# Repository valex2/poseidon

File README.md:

# poseidon
Stanford Robosub 🏄‍♂️🐳🌊 Electrical Subsystem Repository

[Website](https://www.stanfordrobosub.org/)

[Block Diagram](https://drive.google.com/file/d/1UzBXgo1StivMrRFJ6YxzVo7dkJmS1rf_/view?usp=sharing)

# Important notes
## Thrusters
DO NOT RUN THRUSTERS AT FULL POWER FOR THE TIME BEING - 20 to 30% max

DO NOT RUN FOR MORE THAN 10 SECONDS WHILE OUTSIDE OF WATER

## Comms
We are using a Teensy 4.1 that communicates with the Orin over a serial port.

Use serial library in Python, and write as follows:
> portName.write(b"thruster_number delay_value")

### Thruster PWM Assignment
- 1100 us is full reverse thrust
- 1500 us is off
- 1900 us is full forward thrust

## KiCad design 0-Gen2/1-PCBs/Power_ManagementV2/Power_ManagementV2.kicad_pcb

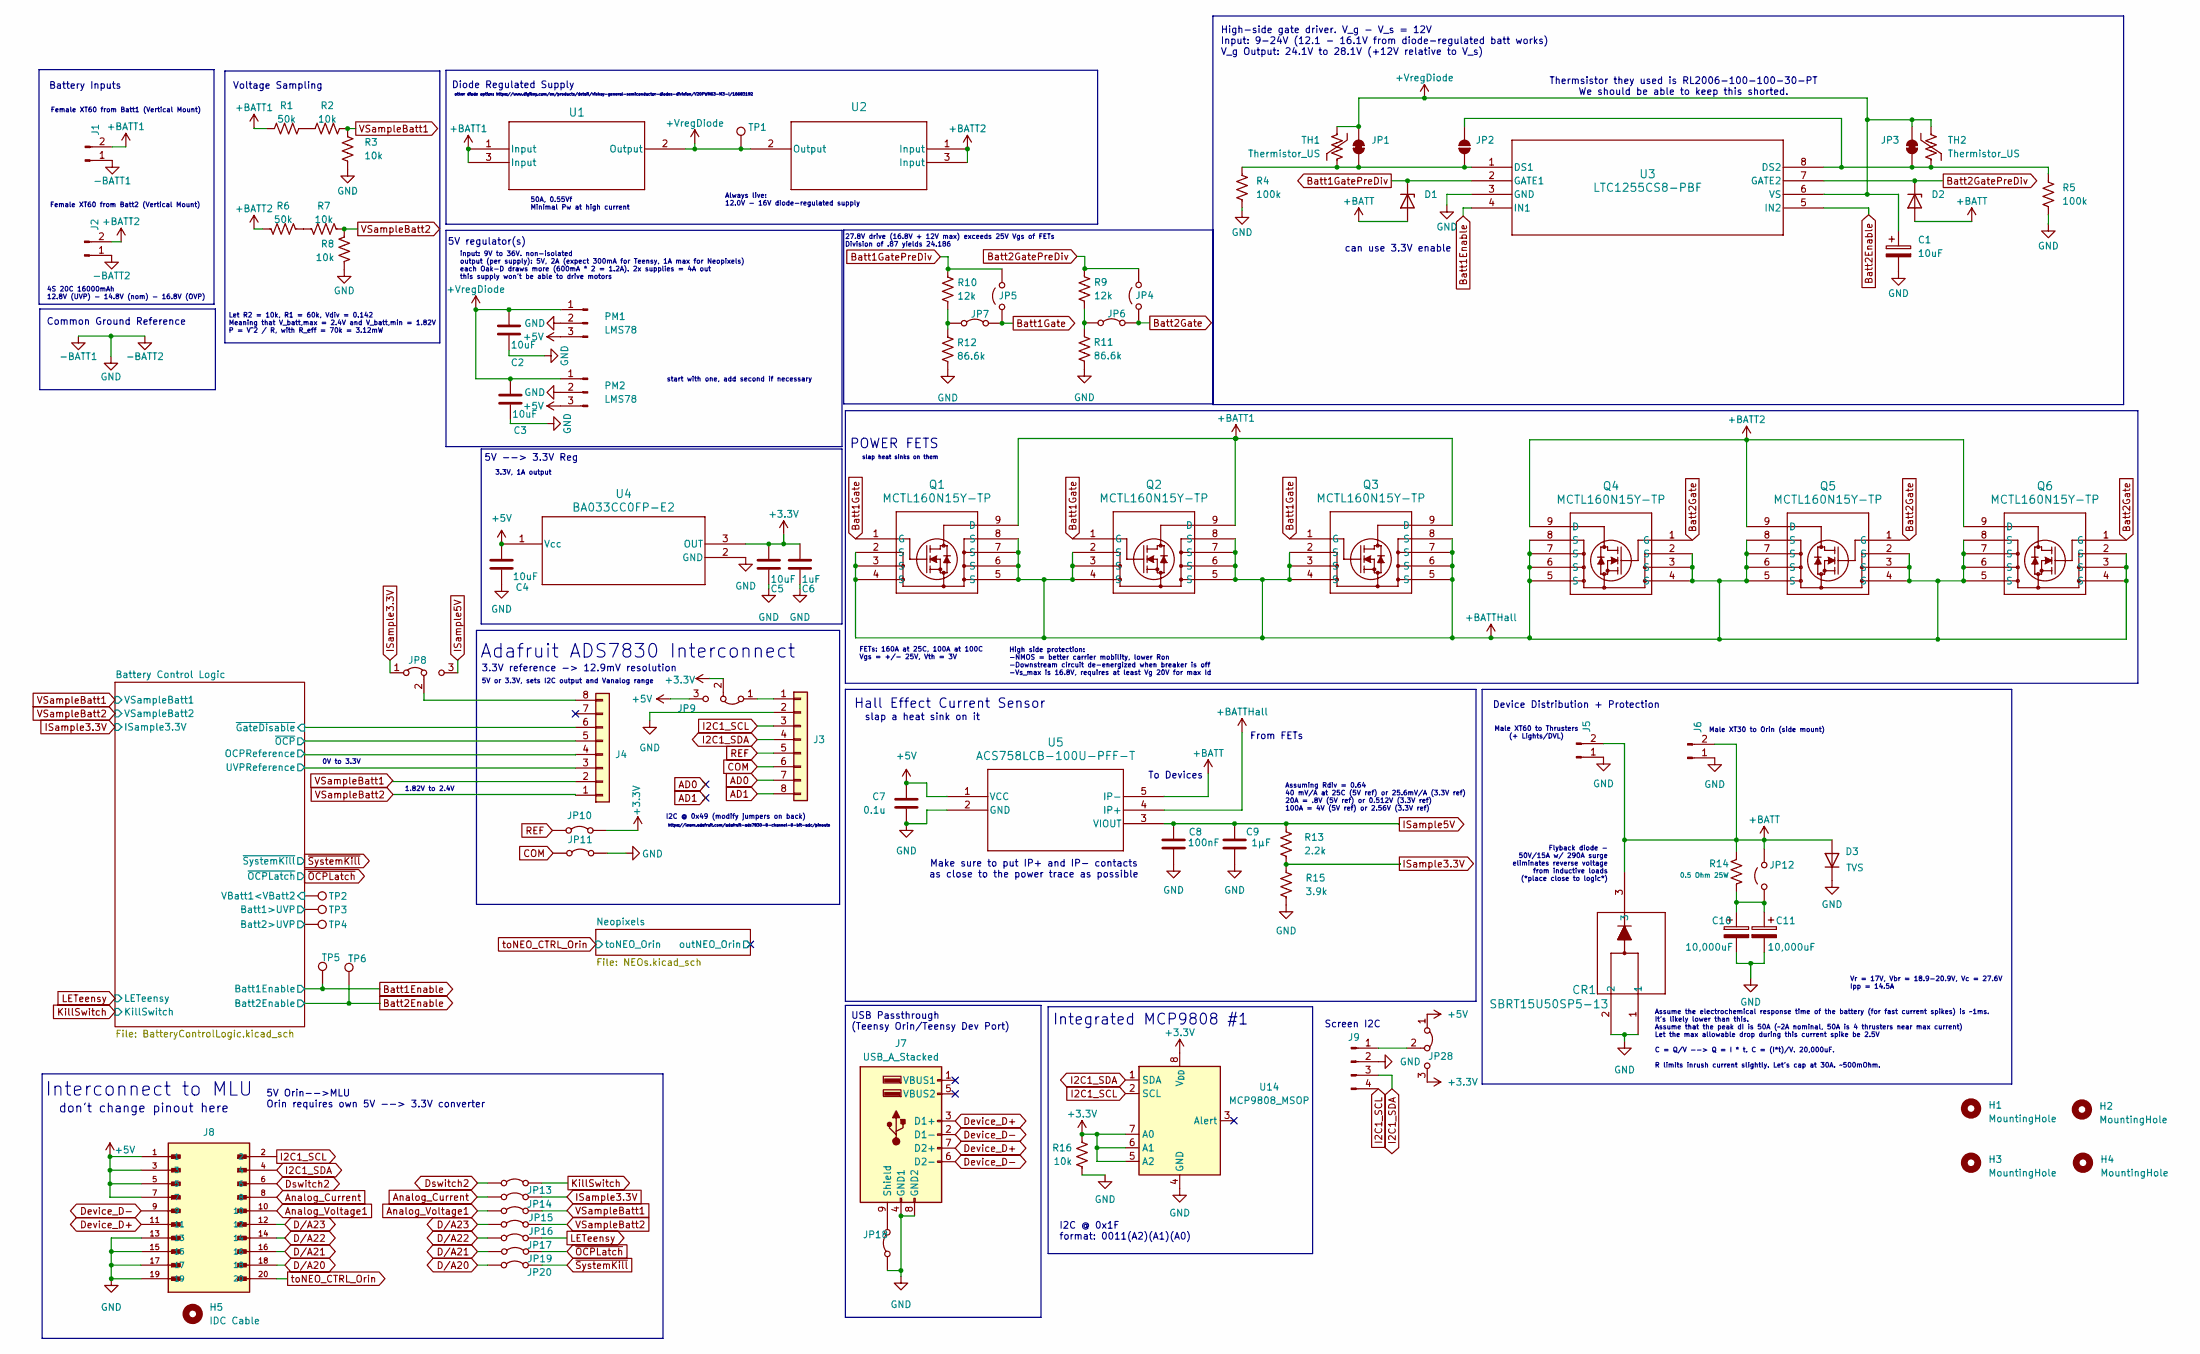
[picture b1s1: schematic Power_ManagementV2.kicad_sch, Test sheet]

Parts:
C1: 10uF; CAP_EEE-1CA100SR_PAN
C2, C3, C4, C5: 10uF; C_0805_2012Metric_Pad1.18x1.45mm_HandSolder
C6: 1uF; C_0805_2012Metric_Pad1.18x1.45mm_HandSolder
C7: 0.1u; C_0805_2012Metric_Pad1.18x1.45mm_HandSolder
C8: 100nF; C_0805_2012Metric_Pad1.18x1.45mm_HandSolder
C9: 1µF; C_0805_2012Metric_Pad1.18x1.45mm_HandSolder
C10, C11: 10,000uF; CP_Radial_D16.0mm_P7.50mm
CR1: SBRT15U50SP5-13; POWERDI5_DIO
D1, D2: D_Zener; 1N5242B
D3: TVS; D_SMA
H1, H2, H3, H4: MountingHole; MountingHole_3.2mm_M3
H5: IDC Cable
J1, J2: Conn_01x02_Pin; AMASS_XT60IPW-M_1x03_P7.20mm_Horizontal
J3, J4: Conn_01x08; PinHeader_1x08_P2.54mm_Vertical
J5: Conn_01x02_Pin; AMASS_XT60PW-F_1x02_P7.20mm_Horizontal
J6: Conn_01x02_Pin; AMASS_XT30PW-F_1x02_P2.50mm_Horizontal
J7: USB_A_Stacked; USB_A_Wuerth_61400826021_Horizontal_Stacked
J8: SBH11-PBPC-D10-ST-BK; SULLINS_SBH11-PBPC-D10-ST-BK; PARTREV J
J9: Conn_01x04_Pin; CONN_SD-43045-008_04_MOL
JP1, JP3: SolderJumper_2_Bridged; SolderJumper-2_P1.3mm_Bridged2Bar_RoundedPad1.0x1.5mm
JP2: SolderJumper_2_Open; SolderJumper-2_P1.3mm_Open_RoundedPad1.0x1.5mm
JP4, JP5: Jumper_2_Open; SolderJumper-2_P1.3mm_Open_RoundedPad1.0x1.5mm
JP6, JP7: Jumper_2_Bridged; SolderJumper-2_P1.3mm_Bridged_RoundedPad1.0x1.5mm
JP8, JP9, JP28: Jumper_3_Bridged12; SolderJumper-3_P1.3mm_Bridged2Bar12_RoundedPad1.0x1.5mm
JP10, JP11, JP13, JP14, JP15, JP16, JP17, JP18, JP19, JP20: Jumper_2_Bridged; SolderJumper-2_P1.3mm_Bridged2Bar_RoundedPad1.0x1.5mm
JP12: Jumper_2_Open; KEYSTONE_5102
PM1, PM2: LMS78
Q1, Q2, Q3, Q4, Q5, Q6: MCTL160N15Y-TP; TOLL-8L_MCC
R1, R6: 50k; R_0805_2012Metric_Pad1.20x1.40mm_HandSolder
R2, R3, R7, R8, R16: 10k; R_0805_2012Metric_Pad1.20x1.40mm_HandSolder
R4, R5: 100k; R_0805_2012Metric
R9, R10: 12k; R_0805_2012Metric_Pad1.20x1.40mm_HandSolder
R11, R12: 86.6k; R_0805_2012Metric_Pad1.20x1.40mm_HandSolder
R13: 2.2k; R_0805_2012Metric_Pad1.20x1.40mm_HandSolder
R14: 0.5 Ohm 25W; TO508P1229X317-3N
R15: 3.9k; R_0805_2012Metric_Pad1.20x1.40mm_HandSolder
TH1, TH2: Thermistor_US; R_0805_2012Metric
TP1: DiodeRegSupply; TestPoint_Keystone_5019_Minature
TP2, TP3, TP4, TP5, TP6: TestPoint; TestPoint_Pad_1.0x1.0mm
U1, U2: STPS5045SG-TR; D2PAK_STM
U3: LTC1255CS8-PBF; LTC1255
U4: BA033CC0FP-E2; TO252-3_ROM
U5: ACS758LCB-100U-PFF-T; Allegro_MicroSystems,_LLC-CB-5-PFF-0-0-MFG
U14: MCP9808_MSOP; MSOP-8_3x3mm_P0.65mm

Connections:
+3.3V: C5.1, C6.1, JP9.2 (C), JP10.2 (B), JP28.3 (B), R16.1, U4.3 (OUT), U14.5 (A2), U14.6 (A1), U14.7 (A0), U14.8 (V_{DD}); also elsewhere on the board
+5V: C4.1, C7.2, J8.1, J8.3, J8.5, J8.7, JP9.3 (B), JP28.1 (A), PM1.3, PM2.3, U4.1 (Vcc), U5.1 (VCC); also elsewhere on the board
+BATT: CR1.3, D1.2 (A), D2.2 (A), D3.2 (A), J5.2, J6.2, JP12.2 (B), R14.1, U5.5 (IP-)
+BATT1: J1.2, Q1.9 (D), Q2.9 (D), Q3.9 (D), R1.2, U1.1 (Input), U1.3 (Input)
+BATT2: J2.2, Q4.9 (D), Q5.9 (D), Q6.9 (D), R6.1, U2.1 (Input), U2.3 (Input)
+BATTHall: Q1.2 (S), Q1.3 (S), Q1.4 (S), Q1.5 (S), Q1.6 (S), Q1.7 (S), Q1.8 (S), Q2.2 (S), Q2.3 (S), Q2.4 (S), Q2.5 (S), Q2.6 (S), Q2.7 (S), Q2.8 (S), Q3.2 (S), Q3.3 (S), Q3.4 (S), Q3.5 (S), Q3.6 (S), Q3.7 (S), Q3.8 (S), Q4.2 (S), Q4.3 (S), Q4.4 (S), Q4.5 (S), Q4.6 (S), Q4.7 (S), Q4.8 (S), Q5.2 (S), Q5.3 (S), Q5.4 (S), Q5.5 (S), Q5.6 (S), Q5.7 (S), Q5.8 (S), Q6.2 (S), Q6.3 (S), Q6.4 (S), Q6.5 (S), Q6.6 (S), Q6.7 (S), Q6.8 (S), U5.4 (IP+)
+VregDiode: C1.1, C2.1, C3.1, JP1.2 (B), JP3.2 (B), PM1.1, PM2.1, TH1.1, TH2.1, TP1.1, U1.2 (Output), U2.2 (Output), U3.6 (VS)
-BATT1: C1.2, C2.2, C3.2, C4.2, C5.2, C6.2, C7.1, C8.2, C9.2, C10.2, C11.2, CR1.1, CR1.2, D3.1 (K), J1.1, J2.1, J3.2, J5.1, J6.1, J7.4 (GND1), J7.8 (GND2), J8.13, J8.15, J8.17, J8.19, J9.2, JP11.2 (B), JP18.1 (A), PM1.2, PM2.2, R3.1, R4.1, R5.1, R8.1, R11.2, R12.2, R15.2, R16.2, U3.3 (GND), U4.2 (GND), U5.2 (GND), U14.4 (GND); also elsewhere on the board
/Battery Control Logic/Batt1>UVP: TP3.1; also elsewhere on the board
/Battery Control Logic/Batt2>UVP: TP4.1; also elsewhere on the board
/Battery Control Logic/OCPReference: J4.4; also elsewhere on the board
/Battery Control Logic/UVPReference: J4.3; also elsewhere on the board
/Battery Control Logic/~GateDisable: J4.6; also elsewhere on the board
/Battery Control Logic/~OCP: J4.5; also elsewhere on the board
AD0: J3.7
AD1: J3.8
Analog_Current: J8.8, JP14.1 (A)
Analog_Voltage1: J8.10, JP15.1 (A)
Batt1Enable: TP5.1, U3.4 (IN1); also elsewhere on the board
Batt1Gate: JP5.1 (A), JP7.2 (B), Q1.1 (G), Q2.1 (G), Q3.1 (G)
Batt1GatePreDiv: D1.1 (K), JP5.2 (B), R10.1, U3.2 (GATE1)
Batt2Enable: TP6.1, U3.5 (IN2); also elsewhere on the board
Batt2Gate: JP4.1 (A), JP6.2 (B), Q4.1 (G), Q5.1 (G), Q6.1 (G)
Batt2GatePreDiv: D2.1 (K), JP4.2 (B), R9.1, U3.7 (GATE2)
COM: J3.6, JP11.1 (A)
Device_D+: J7.3 (D1+), J7.7 (D2+), J8.11
Device_D-: J7.2 (D1-), J7.6 (D2-), J8.9
Dswitch2: J8.6, JP13.1 (A)
D/A20: J8.18, JP20.1 (A)
D/A21: J8.16, JP19.1 (A)
D/A22: J8.14, JP17.1 (A)
D/A23: J8.12, JP16.1 (A)
I2C1_SCL: J3.3, J8.2, J9.4, U14.2 (SCL)
I2C1_SDA: J3.4, J8.4, J9.3, U14.1 (SDA)
ISample3.3V: JP8.1 (A), JP14.2 (B), R13.2, R15.1; also elsewhere on the board
ISample5V: C8.1, C9.1, JP8.3 (B), R13.1, U5.3 (VIOUT)
KillSwitch: JP13.2 (B); also elsewhere on the board
LETeensy: JP17.2 (B); also elsewhere on the board
unnamed: J3.1, JP9.1 (A)
unnamed: J4.8, JP8.2 (C)
unnamed: J7.9 (Shield), JP18.2 (B)
unnamed: J9.1, JP28.2 (C)
unnamed: JP1.1 (A), JP2.1 (A), R4.2, TH1.2, U3.1 (DS1)
unnamed: JP2.2 (B), JP3.1 (A), R5.2, TH2.2, U3.8 (DS2)
unnamed: JP6.1 (A), R9.2, R11.1
unnamed: JP7.1 (A), R10.2, R12.1
unnamed: C10.1, C11.1, JP12.1 (A), R14.2
unnamed: R1.1, R2.1
unnamed: R6.2, R7.2
REF: J3.5, JP10.1 (A)
VSampleBatt1: J4.2, JP15.2 (B), R2.2, R3.2; also elsewhere on the board
VSampleBatt2: J4.1, JP16.2 (B), R7.1, R8.2; also elsewhere on the board
toNEO_CTRL_Orin: J8.20; also elsewhere on the board
~OCPLatch: JP19.2 (B); also elsewhere on the board
~SystemKill: JP20.2 (B); also elsewhere on the board

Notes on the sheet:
Hall Effect Current Sensor
0V to 3.3V
slap heat sinks on them
Screen I2C
USB Passthrough (Teensy Orin/Teensy Dev Port)
Female XT60 from Batt2 (Vertical Mount)
Integrated MCP9808 #1
5V Orin-->MLU Orin requires own 5V --> 3.3V converter
start with one, add second if necessary
Let R2 = 10k, R1 = 60k, Vdiv = 0.142 Meaning that V_batt,max = 2.4V and V_batt,min = 1.82V P = V^2 / R, with R_eff = 70k = 3.12mW
input: 9V to 36V. non-isolated output (per supply): 5V, 2A (expect 300mA for Teensy, 1A max for Neopixels) each Oak-D draws more (600mA * 2 = 1.2A). 2x supplies = 4A out this supply won't be able to drive motors
50A, 0.55Vf Minimal Pw at high current
I2C @ 0x1F format: 0011(A2)(A1)(A0)
Always live: 12.0V - 16V diode-regulated supply
Battery Inputs
can use 3.3V enable
To Devices
I2C @ 0x49 (modify jumpers on back)
Female XT60 from Batt1 (Vertical Mount)
Interconnect to MLU
FETs: 160A at 25C, 100A at 100C Vgs = +/- 25V, Vth = 3V
Male XT60 to Thrusters (+ Lights/DVL)
Voltage Sampling
Common Ground Reference
Device Distribution + Protection
Thermsistor they used is RL2006-100-100-30-PT We should be able to keep this shorted.
5V --> 3.3V Reg
Adafruit ADS7830 Interconnect
POWER FETS
Assuming Rdiv = 0.64 40 mV/A at 25C (5V ref) or 25.6mV/A (3.3V ref) 20A = .8V (5V ref) or 0.512V (3.3V ref) 100A = 4V (5V ref) or 2.56V (3.3V ref)
4S 20C 16000mAh 12.8V (UVP) - 14.8V (nom) - 16.8V (OVP)
slap a heat sink on it
Assume the electrochemical response time of the battery (for fast current spikes) is ~1ms. It's likely lower than this. Assume that the peak dI is 50A (~2A nominal, 50A is 4 thrusters near max current) Let the max allowable drop during this current spike be 2.5V C = Q/V --> Q = I * t. C = (I*t)/V. 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
Diode Regulated Supply
5V or 3.3V, sets I2C output and Vanalog range
27.8V drive (16.8V + 12V max) exceeds 25V Vgs of FETs Division of .87 yields 24.186
Flyback diode - 50V/15A w/ 290A surge eliminates reverse voltage from inductive loads (*place close to logic*)
Vr = 17V, Vbr = 18.9-20.9V, Vc = 27.6V Ipp = 14.5A
Make sure to put IP+ and IP- contacts as close to the power trace as possible
3.3V reference -> 12.9mV resolution

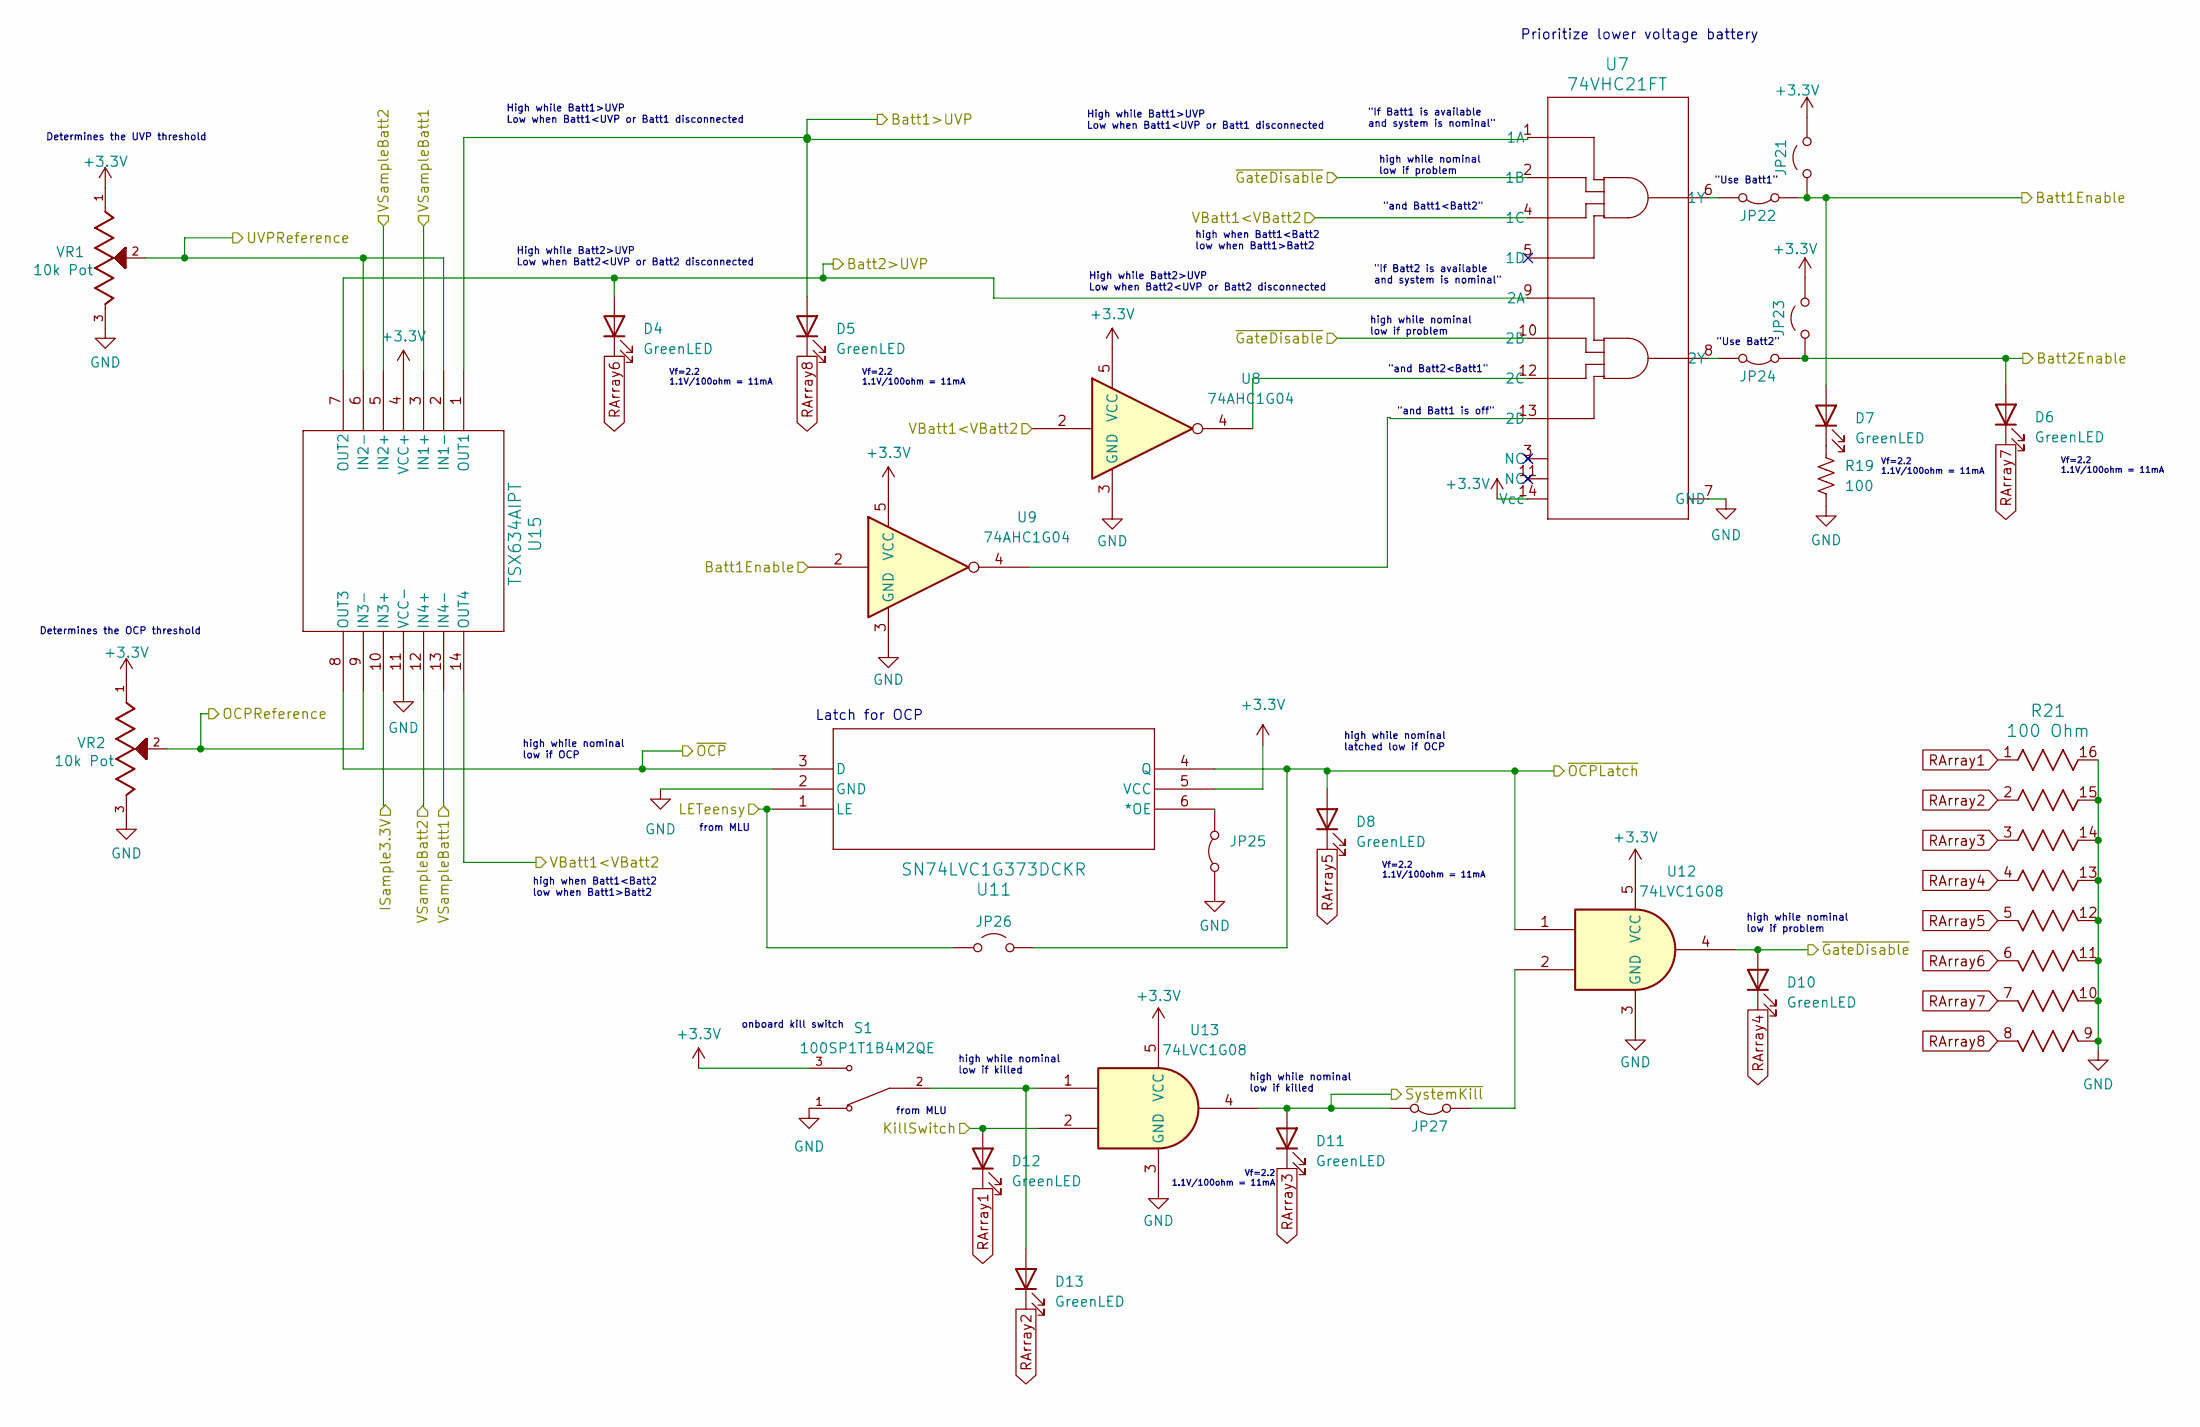
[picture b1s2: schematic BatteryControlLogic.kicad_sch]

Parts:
D4, D5, D6, D7, D8, D10, D11, D12, D13: GreenLED; LED_0603_1608Metric_Pad1.05x0.95mm_HandSolder
JP21, JP23, JP26: Jumper_2_Open; SolderJumper-2_P1.3mm_Open_RoundedPad1.0x1.5mm
JP22, JP24, JP25, JP27: Jumper_2_Bridged; SolderJumper-2_P1.3mm_Bridged2Bar_RoundedPad1.0x1.5mm
R19: 100; R_0805_2012Metric_Pad1.20x1.40mm_HandSolder
R21: 100 Ohm; 2506_8x_Resistor_Array
S1: 100SP1T1B4M2QE; SW_100SP1T1B4M2QE; PARTREV E
U7: 74VHC21FT; TSSOP14B
U8, U9: 74AHC1G04; SOT-353_SC-70-5_Handsoldering
U11: SN74LVC1G373DCKR; SN74LVC
U12, U13: 74LVC1G08; SOT-353_SC-70-5_Handsoldering
U15: TSX634AIPT; TSSOP14_STM
VR1, VR2: 3296W-1-103RLF; TRIM_3296W-1-103RLF; PARTREV 05/16

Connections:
+3.3V: JP21.2 (B), JP23.2 (B), S1.3, U7.14 (Vcc), U8.5 (VCC), U9.5 (VCC), U11.5 (VCC), U12.5 (VCC), U13.5 (VCC), U15.4 (VCC+), VR1.1, VR2.1; also elsewhere on the board
-BATT1: JP25.1 (A), R19.2, R21.9, R21.10, R21.11, R21.12, R21.13, R21.14, R21.15, R21.16, S1.1, U7.7 (GND), U8.3 (GND), U9.3 (GND), U11.2 (GND), U12.3 (GND), U13.3 (GND), U15.11 (VCC-), VR1.3, VR2.3; also elsewhere on the board
/Battery Control Logic/Batt1>UVP: D5.2 (A), U7.1 (1A), U15.1 (OUT1); also elsewhere on the board
/Battery Control Logic/Batt2>UVP: D4.2 (A), U7.9 (2A), U15.7 (OUT2); also elsewhere on the board
/Battery Control Logic/OCPReference: U15.9 (IN3-), VR2.2; also elsewhere on the board
/Battery Control Logic/UVPReference: U15.2 (IN1-), U15.6 (IN2-), VR1.2; also elsewhere on the board
/Battery Control Logic/VBatt1<VBatt2: U7.4 (1C), U8.2, U15.14 (OUT4)
/Battery Control Logic/~GateDisable: D10.2 (A), U7.2 (1B), U7.10 (2B), U12.4; also elsewhere on the board
/Battery Control Logic/~OCP: U11.3 (D), U15.8 (OUT3); also elsewhere on the board
Batt1Enable: D7.2 (A), JP21.1 (A), JP22.2 (B), U9.2; also elsewhere on the board
Batt2Enable: D6.2 (A), JP23.1 (A), JP24.2 (B); also elsewhere on the board
ISample3.3V: U15.10 (IN3+); also elsewhere on the board
KillSwitch: D12.2 (A), U13.2; also elsewhere on the board
LETeensy: JP26.1 (A), U11.1 (LE); also elsewhere on the board
unnamed: D7.1 (K), R19.1
unnamed: D13.2 (A), S1.2, U13.1
unnamed: JP22.1 (A), U7.6 (1Y)
unnamed: JP24.1 (A), U7.8 (2Y)
unnamed: JP25.2 (B), U11.6 (*OE)
unnamed: JP27.2 (B), U12.2
unnamed: U7.12 (2C), U8.4
unnamed: U7.13 (2D), U9.4
RArray1: D12.1 (K), R21.1
RArray2: D13.1 (K), R21.2
RArray3: D11.1 (K), R21.3
RArray4: D10.1 (K), R21.4
RArray5: D8.1 (K), R21.5
RArray6: D4.1 (K), R21.6
RArray7: D6.1 (K), R21.7
RArray8: D5.1 (K), R21.8
VSampleBatt1: U15.3 (IN1+), U15.13 (IN4-); also elsewhere on the board
VSampleBatt2: U15.5 (IN2+), U15.12 (IN4+); also elsewhere on the board
~OCPLatch: D8.2 (A), JP26.2 (B), U11.4 (Q), U12.1; also elsewhere on the board
~SystemKill: D11.2 (A), JP27.1 (A), U13.4; also elsewhere on the board

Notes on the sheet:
Determines the UVP threshold
onboard kill switch
"If Batt1 is available and system is nominal"
Vf=2.2 1.1V/100ohm = 11mA
high when Batt1<Batt2 low when Batt1>Batt2
high while nominal low if problem
High while Batt1>UVP Low when Batt1<UVP or Batt1 disconnected
high while nominal low if killed
"and Batt1<Batt2"
from MLU
"Use Batt2"
"Use Batt1"
high while nominal latched low if OCP
Prioritize lower voltage battery
High while Batt2>UVP Low when Batt2<UVP or Batt2 disconnected
Determines the OCP threshold
"and Batt1 is off"
"If Batt2 is available and system is nominal"
Latch for OCP
"and Batt2<Batt1"
high while nominal low if OCP

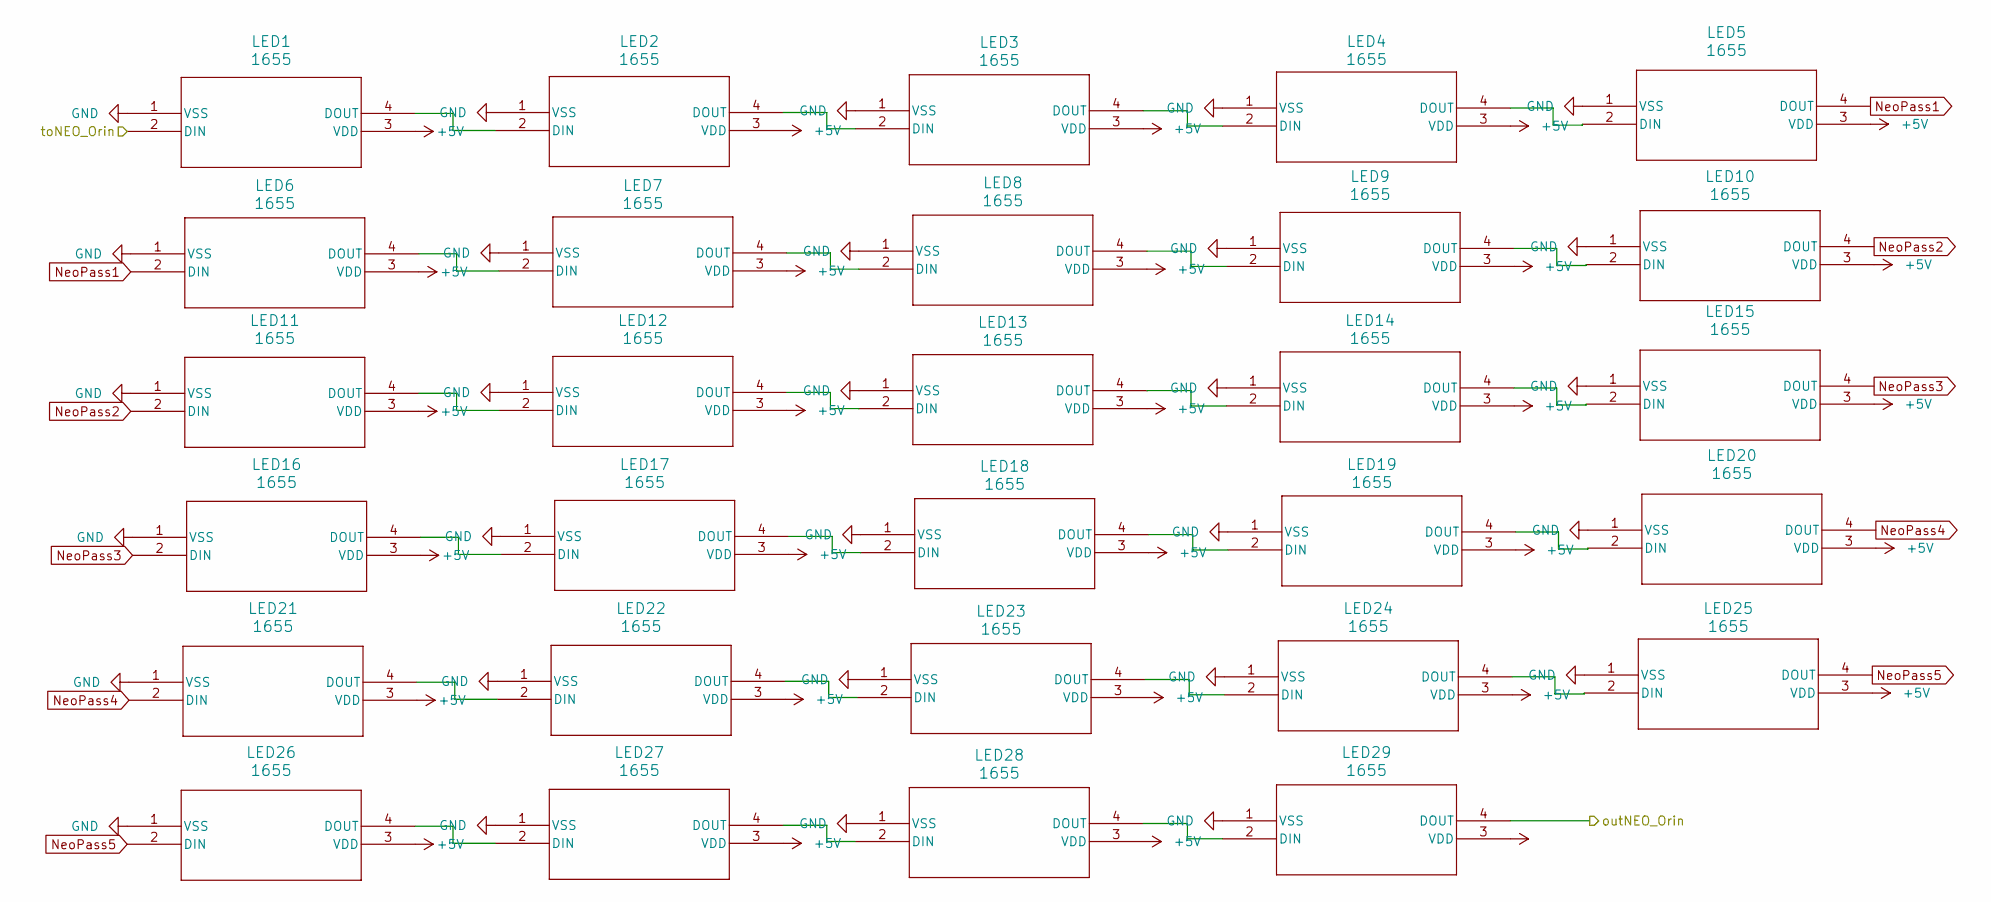
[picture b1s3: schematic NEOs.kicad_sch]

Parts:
LED1, LED2, LED3, LED4, LED5, LED6, LED7, LED8, LED9, LED10, LED11, LED12, LED13, LED14, LED15, LED16, LED17, LED18, LED19, LED20, LED21, LED22, LED23, LED24, LED25, LED26, LED27, LED28, LED29: 1655; LED_LiteOn_LTST-E563C_PLCC4_5.0x5.0mm_P3.2mm_HandSoldering

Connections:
+5V: LED1.3 (VDD), LED2.3 (VDD), LED3.3 (VDD), LED4.3 (VDD), LED5.3 (VDD), LED6.3 (VDD), LED7.3 (VDD), LED8.3 (VDD), LED9.3 (VDD), LED10.3 (VDD), LED11.3 (VDD), LED12.3 (VDD), LED13.3 (VDD), LED14.3 (VDD), LED15.3 (VDD), LED16.3 (VDD), LED17.3 (VDD), LED18.3 (VDD), LED19.3 (VDD), LED20.3 (VDD), LED21.3 (VDD), LED22.3 (VDD), LED23.3 (VDD), LED24.3 (VDD), LED25.3 (VDD), LED26.3 (VDD), LED27.3 (VDD), LED28.3 (VDD), LED29.3 (VDD); also elsewhere on the board
-BATT1: LED1.1 (VSS), LED2.1 (VSS), LED3.1 (VSS), LED4.1 (VSS), LED5.1 (VSS), LED6.1 (VSS), LED7.1 (VSS), LED8.1 (VSS), LED9.1 (VSS), LED10.1 (VSS), LED11.1 (VSS), LED12.1 (VSS), LED13.1 (VSS), LED14.1 (VSS), LED15.1 (VSS), LED16.1 (VSS), LED17.1 (VSS), LED18.1 (VSS), LED19.1 (VSS), LED20.1 (VSS), LED21.1 (VSS), LED22.1 (VSS), LED23.1 (VSS), LED24.1 (VSS), LED25.1 (VSS), LED26.1 (VSS), LED27.1 (VSS), LED28.1 (VSS), LED29.1 (VSS); also elsewhere on the board
/Neopixels/outNEO_Orin: LED29.4 (DOUT)
NeoPass1: LED5.4 (DOUT), LED6.2 (DIN)
NeoPass2: LED10.4 (DOUT), LED11.2 (DIN)
NeoPass3: LED15.4 (DOUT), LED16.2 (DIN)
NeoPass4: LED20.4 (DOUT), LED21.2 (DIN)
NeoPass5: LED25.4 (DOUT), LED26.2 (DIN)
unnamed: LED1.4 (DOUT), LED2.2 (DIN)
unnamed: LED2.4 (DOUT), LED3.2 (DIN)
unnamed: LED3.4 (DOUT), LED4.2 (DIN)
unnamed: LED4.4 (DOUT), LED5.2 (DIN)
unnamed: LED6.4 (DOUT), LED7.2 (DIN)
unnamed: LED7.4 (DOUT), LED8.2 (DIN)
unnamed: LED8.4 (DOUT), LED9.2 (DIN)
unnamed: LED9.4 (DOUT), LED10.2 (DIN)
unnamed: LED11.4 (DOUT), LED12.2 (DIN)
unnamed: LED12.4 (DOUT), LED13.2 (DIN)
unnamed: LED13.4 (DOUT), LED14.2 (DIN)
unnamed: LED14.4 (DOUT), LED15.2 (DIN)
unnamed: LED16.4 (DOUT), LED17.2 (DIN)
unnamed: LED17.4 (DOUT), LED18.2 (DIN)
unnamed: LED18.4 (DOUT), LED19.2 (DIN)
unnamed: LED19.4 (DOUT), LED20.2 (DIN)
unnamed: LED21.4 (DOUT), LED22.2 (DIN)
unnamed: LED22.4 (DOUT), LED23.2 (DIN)
unnamed: LED23.4 (DOUT), LED24.2 (DIN)
unnamed: LED24.4 (DOUT), LED25.2 (DIN)
unnamed: LED26.4 (DOUT), LED27.2 (DIN)
unnamed: LED27.4 (DOUT), LED28.2 (DIN)
unnamed: LED28.4 (DOUT), LED29.2 (DIN)
toNEO_CTRL_Orin: LED1.2 (DIN); also elsewhere on the board

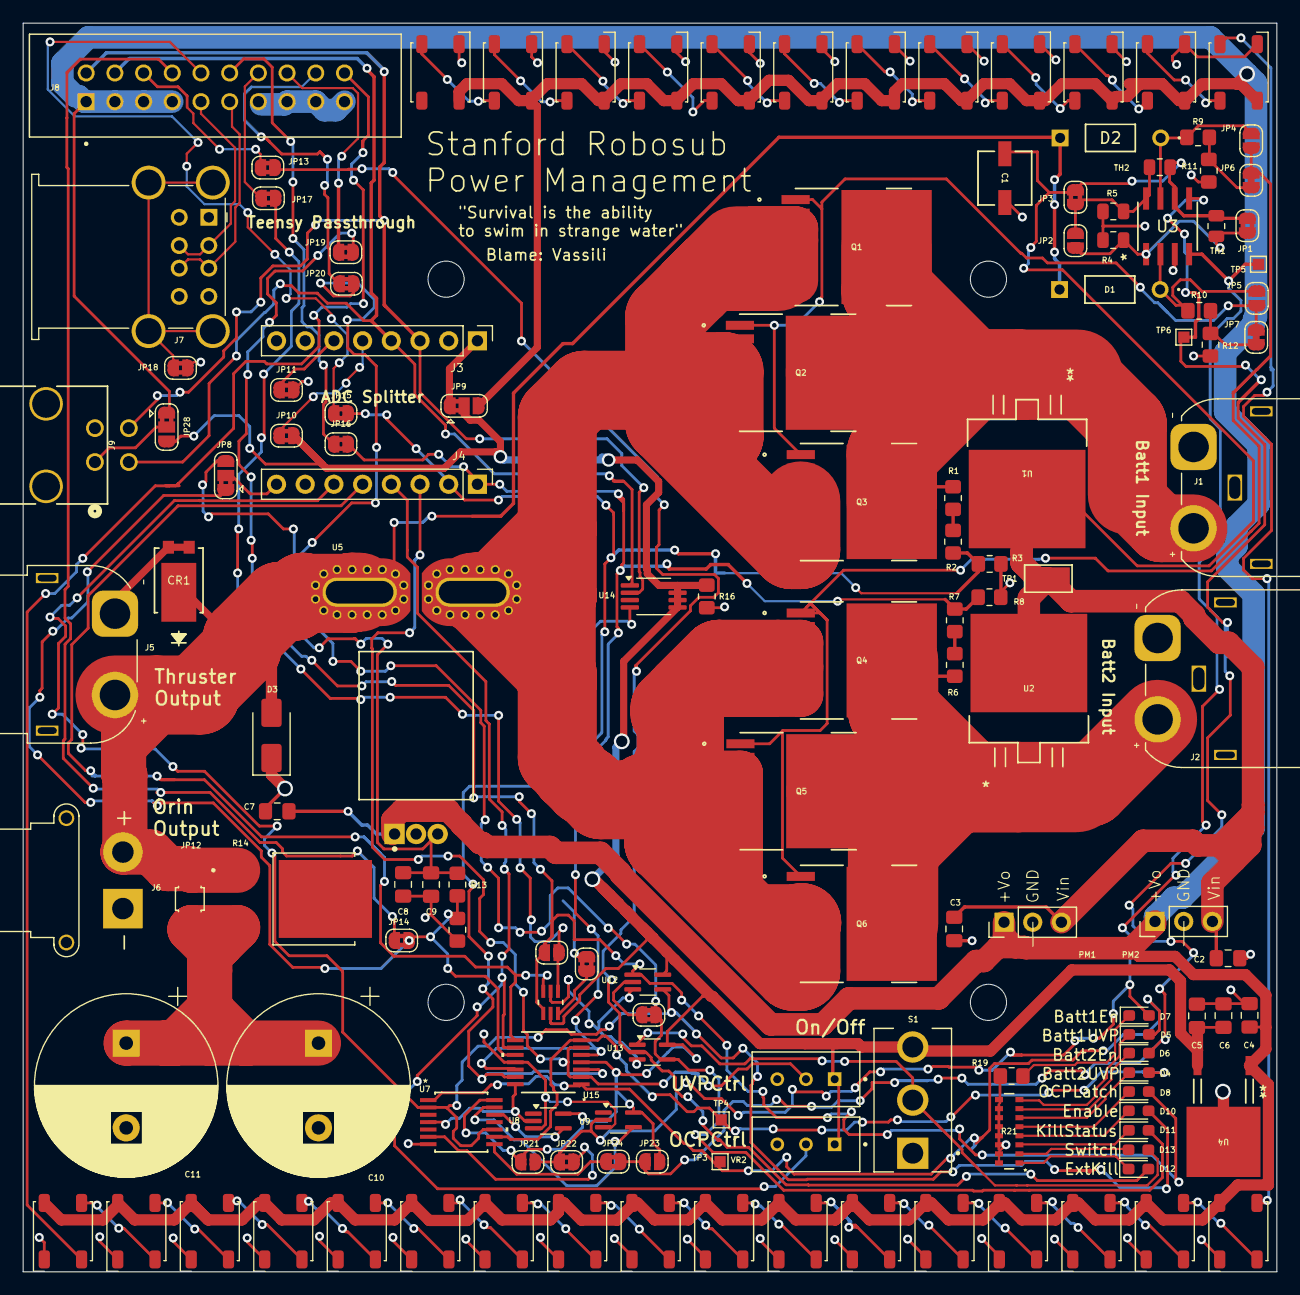
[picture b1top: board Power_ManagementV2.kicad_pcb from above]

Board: 2 copper layers, 110.9 x 110.5 mm, 143 parts (0 on the bottom side), 98 nets.

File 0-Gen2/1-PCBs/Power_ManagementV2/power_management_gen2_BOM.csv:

"Reference","Value","Qty","Supplier 1","Supplier 1 S/N"
"C1","10uF","1","https://www.digikey.com/en/products/detail/panasonic-electro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","PCE3878CT-ND"
"C2,C3,C4,C5,C6","-- mixed values --","5","https://www.digikey.com/en/products/detail/murata-electronic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","490-6473-1-ND"
"C7","0.1u","1","https://www.digikey.com/en/products/detail/samsung-electro-m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","1276-1003-1-ND"
"C8","100nF","1","https://www.digikey.com/en/products/detail/yageo/CC0805KRX7R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","311-1140-1-ND"
"C9","1µF","1","https://www.digikey.com/en/products/detail/samsung-electro-m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","1276-1029-1-ND"
"C10,C11","10,000uF","2","https://www.digikey.com/en/products/detail/rubycon/16PX10000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","1189-1125-ND"
"CR1","SBRT15U50SP5-13","1","https://www.digikey.com/en/products/detail/diodes-incorporat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","SBRT15U50SP5-13DICT-ND"
"D1,D2","D_Zener","2","https://www.digikey.com/en/products/detail/onsemi/1N5242B/977596","1N5242B-ND"
"D3","TVS","1","https://www.digikey.com/en/products/detail/bourns-inc/SMAJ17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","SMAJ17ABCT-ND"
"D4,D5,D6,D7,D8,D10,D11,D12,D13","GreenLED","9","https://www.digikey.com/en/products/detail/rohm-semiconducto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","846-SML-D12P8WT86CT-ND"
"H1,H2,H3,H4,J1,J2,J3,J4,J5,J6,J9,JP4,JP5,JP6,JP7,JP10,JP11,JP13,JP14,JP15,JP16,JP17,JP18,JP19,JP20,JP21,JP22,JP23,JP24,JP25,JP26,JP27,LED1,LED2,LED3,LED4,LED5,LED6,LED7,LED8,LED9,LED10,LED11,LED12,LED13,LED14,LED15,LED16,LED17,LED18,LED19,LED20,LED21,LED22,LED23,LED24,LED25,LED26,LED27,LED28,LED29,TP1,TP2,TP3,TP4,TP5,TP6","-- mixed values --","67","",""
"J7","USB_A_Stacked","1","https://www.digikey.com/en/products/detail/assmann-wsw-compo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","AE11131-ND"
"J8","SBH11-PBPC-D10-ST-BK","1","https://www.digikey.com/en/products/detail/sullins-connector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","S9172-ND"
"JP12","Jumper_2_Open","1","https://www.digikey.com/en/products/detail/keystone-electron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","36-5102-ND"
"PM1,PM2","LMS78","2","https://www.digikey.com/en/products/detail/gaptec-electronic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","3182-LMS78_05-2.0R-ND"
"Q1,Q2,Q3,Q4,Q5,Q6","MCTL160N15Y-TP","6","https://www.digikey.com/en/products/detail/micro-commercial-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","353-MCTL160N15Y-TPCT-ND"
"R1,R6","50k","2","https://www.digikey.com/en/products/detail/vishay-dale-thin-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","764-1535-1-ND"
"R2,R3,R7,R8","10k","4","https://www.digikey.com/en/products/detail/susumu/RR1220P-10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","RR12P10.0KDCT-ND"
"R4,R5","100k","2","https://www.digikey.com/en/products/detail/yageo/RC0805FR-07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","311-100KCRCT-ND"
"R9,R10","12k","2","https://www.digikey.com/en/products/detail/stackpole-electro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","738-RMCF0805JT12K0CT-ND"
"R11,R12","86.6k","2","https://www.digikey.com/en/products/detail/yageo/RC0805FR-07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","311-86.6KCRCT-ND"
"R13","2.2k","1","https://www.digikey.com/en/products/detail/te-connectivity-p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","A106060CT-ND"
"R14","0.5 Ohm 25W","1","https://www.digikey.com/en/products/detail/bourns-inc/PWR163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","118-PWR163S-25-R500FECT-ND"
"R15","3.9k","1","https://www.digikey.com/en/products/detail/te-connectivity-p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","A126369CT-ND"
"R16","10k","1","https://www.digikey.com/en/products/detail/panasonic-electro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","P10KACT-ND"
"R19","100","1","https://www.digikey.com/en/products/detail/yageo/RC0805FR-07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","311-100CRCT-ND"
"R21","100 Ohm","1","https://www.digikey.com/en/products/detail/cts-resistor-prod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","60-742C163101JPCT-ND"
"S1","100SP1T1B4M2QE","1","https://www.digikey.com/en/products/detail/e-switch/100SP1T1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","EG2355-ND"
"TH1,TH2","Thermistor_US","2","https://www.digikey.com/en/products/detail/yageo/RC0805FR-07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","311-150CRCT-ND"
"U1,U2","STPS5045SG-TR","2","https://www.digikey.com/en/products/detail/stmicroelectronic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","497-13279-1-ND"
"U3","LTC1255CS8-PBF","1","https://www.digikey.com/en/products/detail/analog-devices-in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","LTC1255CS8#PBF-ND"
"U4","BA033CC0FP-E2","1","https://www.digikey.com/en/products/detail/rohm-semiconducto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","BA033CC0FP-E2CT-ND"
"U5","ACS758LCB-100U-PFF-T","1","https://www.digikey.com/en/products/detail/allegro-microsyst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","620-1354-ND"
"U7","74VHC21FT","1","https://www.digikey.com/en/products/detail/toshiba-semicondu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","74VHC21FTCT-ND"
"U8,U9","74AHC1G04","2","https://www.digikey.com/en/products/detail/texas-instruments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","296-11600-1-ND"
"U11","SN74LVC1G373DCKR","1","https://www.digikey.com/en/products/detail/texas-instruments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","296-18775-1-ND"
"U12,U13","74LVC1G08","2","https://www.digikey.com/en/products/detail/texas-instruments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","296-11602-1-ND"
"U14","MCP9808_MSOP","1","https://www.digikey.com/en/products/detail/microchip-technol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","MCP9808T-E/MSCT-ND"
"U15","TSX634AIPT","1","https://www.digikey.com/en/products/detail/stmicroelectronic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","497-14067-1-ND"
"VR1,VR2","3296W-1-103RLF","2","https://www.digikey.com/en/products/detail/bourns-inc/3296W-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","118-3296W-1-103RLFCT-ND"

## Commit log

2024-04-12 update[readme]
2024-04-12 populate[github]
2024-04-15 manuals
2024-04-19 updated requirements.txt
2024-04-26 thrust_pwm.ino
    fix PWM addressing, working version
2024-04-26 update[readme for PWM]
2024-05-03 add[thrust_board]
2024-05-03 including board EDA
2024-05-11 Create thrust_pwm_sensor.ino
    pwm assignment code that includes reading from voltage and pressure sensor
2024-05-17 test pwm in terminal
2024-05-17 works instantly!
2024-05-25 RC controller code
    This is the code to control motors through RC controller (has not been tested yet with teensy wired to motors)
2024-05-27 ryota's i2c code
2024-05-27 include display and light/switch functionality
2024-06-30 save[power distribution board rev1]
2024-06-30 rename and reorganize
2024-06-30 power rev2[fix diodes, ground loop, silkscreen]
2024-06-30 rev2[ready]
2024-06-30 rev2 [final]
2024-07-01 rev2 -ok2fab
2024-07-03 restructuring github
2024-07-03 updating readme
2024-07-03 adding dvl stuff
2024-07-03 fix[software kill switch]
2024-07-13 adding ryota board
2024-07-14 teensy board schematic
2024-07-15 v1 ok2fab
2024-08-07 pre-competition save
2024-08-29 adding ryota leak detect
2024-08-29 kevin idiot
2024-08-30 working
2024-08-30 plotting updates
2024-09-07 data from MBARI
2024-10-23 for Fabi
2024-10-30 draft of connecting board with current sensors
    I'm still waiting to get an email back for the footprint of the connector pins but i have a good one saved.
2024-11-07 Final Power Dist Board
2024-11-07 pushing current management board
2024-11-07 Finished and Tested
2024-11-15 done with management
2024-11-15 good spot
2024-11-28 BOM changes
2025-01-23 Jermaine's Update v2_teensy_code.ino with local changes
2025-01-29 pcb to fit dimensions
2025-02-01 syncing
2025-02-01 adding Jermainestuff
2025-02-01 saving
2025-02-01 tweaking board
2025-02-02 Rev2 on Power Distribution Complete
2025-02-05 MLU breakout in progress
2025-02-11 MLU progress
2025-02-12 layout done
2025-02-12 done with MLU
2025-02-12 syncing data
2025-02-14 pushing PWM code
2025-02-16 Update simple_pwm.ino
    fixed transaction message to match Orin expectations
2025-02-20 pushing most recent
2025-02-20 almost there
2025-03-01 sw_stack sd modifications
2025-03-01 before major SD modifications
2025-03-02 progress on data logging
2025-03-02 deleting old files
2025-03-02 before adding display code
2025-03-02 updated code
2025-03-02 past plotting
2025-04-09 Add files via upload
    most updated sw code, e-bay re-design 3
2025-04-11 sw_stack -- TODO, ADS7890, fix depth
2025-04-11 need to fix packet drop and DVL
2025-04-16 pushing
2025-04-16 dvl script
2025-04-19 push before merge
2025-04-19 [clean] force reset main to track my unstable branch
2025-04-19 [clean] repo hygeine
2025-04-19 [clean] delete .vscode directory
2025-04-19 [add] neopix linear testing
2025-04-19 [add] block diagram
2025-04-24 neo_strobing
2025-05-04 [update] stable_code NEO/LIGHT, v2 start for boards
2025-05-04 [update] attempt integrating firmware
2025-05-04 [bugfix] some modifications/improvements to working code
2025-05-07 [bug fix] added initilization check for depth sensor
2025-05-09 [add] MLU2 progress, [bugfix] depth sensor
2025-05-09 [add] MLUv2 Updates, [bugfix] depthsensor
2025-05-09 [bugfix] depth via BME 0x76 removal, [add] MLUv2 progress
2025-05-13 [changes] MLUv2
2025-05-13 quick save
2025-05-14 [add] major layout updates
2025-05-14 [final pass] MLU breakout
2025-05-14 [add] beginning routing
2025-05-15 before restructure
2025-05-15 [bugfix] rescued footprints
2025-05-16 before renumbering LEDs
2025-05-16 routing
2025-05-16 initial routing done
2025-05-19 [add] silkscreen modifications to power distribution
2025-05-21 added automatic shutdown for servos
2025-05-22 add managementv2
2025-05-22 [add] staroddi for software
2025-05-22 updating
2025-05-22 progress distribution
2025-05-23 management2 updates
2025-05-23 hotswap modifications
2025-05-30 almost ready to fab
2025-05-30 cleaned up circuit
2025-05-31 almost done with layout
2025-05-31 done with dist
2025-06-03 almost done with all orders
2025-06-04 ready for fab
2025-06-05 some updates
2025-06-06 board updates
2025-06-24 [bugfixing] board bringup
2025-07-10 cleaned up firmware code and uploaded to STABLE; CURRENT SUB HAS THE STABLE CODE UPLOADED
2025-07-11 fixed thruster logging and added lumen light capability
2025-08-13 fixed a few code for robosub 2025 comp
2025-08-14 [add] comp modifications
2025-08-14 [add] squirt, todo fix waiting
2025-08-14 before big squirt changes
2025-08-14 making logs better
2025-08-14 entire mission planning
2025-08-14 some modifications
2025-08-14 first test save
2025-08-15 before adding faster kill
2025-08-15 fixed kill switch to interrupt
2025-08-15 servo ramps, mission planner bugs
2025-08-15 added torpedo functionality
2025-08-15 added torpedo capabilities
2025-08-15 actually implemented hiroshima and nagasaki
2025-08-15 some squirt updates
2025-08-15 dropper functioning
2025-08-16 before interrupts and squirt updates
2025-08-16 squirt kill updates
2025-08-16 squirt kill working
2025-08-16 added torpedo and kill switch fix
2025-08-16 before squirt changes
2025-08-16 squirt with kill switch execution
2025-08-18 pushing after comp
